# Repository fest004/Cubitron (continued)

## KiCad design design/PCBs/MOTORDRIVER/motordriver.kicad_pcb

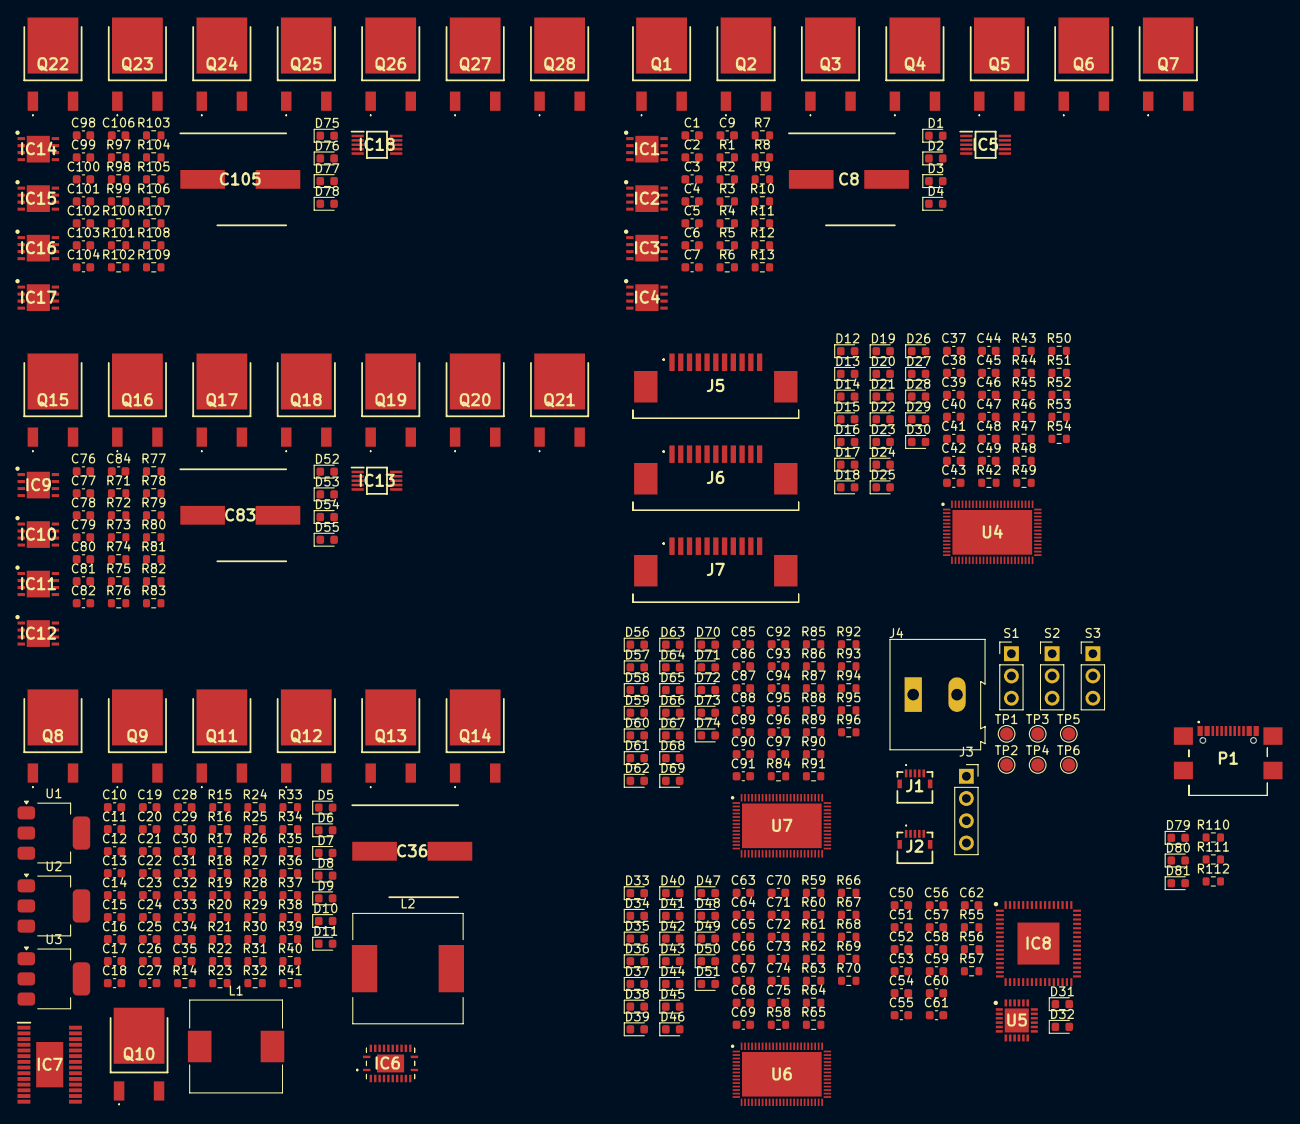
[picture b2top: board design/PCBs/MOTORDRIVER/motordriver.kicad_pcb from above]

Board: 4 copper layers, 371 parts (0 on the bottom side), 222 nets, no tracks yet.

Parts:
C1, C4, C6, C9, C15, C17, C24, C25, C76, C79, C81, C84, C98, C101, C103, C106: 0.1µF; C_0603_1608Metric
C2, C3, C5, C7, C18, C19, C23, C77, C78, C80, C82, C99, C100, C102, C104: 1µF; C_0603_1608Metric
C8, C36, C83, C105: 220µF 35V; CAPAE1050X1050N
C10, C16, C22, C34, C35, C40, C41, C42, C43, C44, C45, C46, C47, C48, C50, C52, C54, C56, C58, C60, C62, C66, C67, C68, C69, C70, C71, C72, C73, C74, C88, C89, C90, C91, C92, C93, C94, C95, C96: 100nF; C_0603_1608Metric
C11, C12: 2.2µF; C_0603_1608Metric
C13, C20, C26: 10uF; C_0603_1608Metric
C14, C27, C28, C51, C53, C55, C57, C59: 10µF; C_0603_1608Metric
C21: 0.047µF; C_0603_1608Metric
C29, C49, C75, C97: 10nF; C_0603_1608Metric
C30: 33nF; C_0603_1608Metric
C31: 470pF; C_0603_1608Metric
C32: 15nF; C_0603_1608Metric
C33: 220pF; C_0603_1608Metric
C37, C38, C39, C63, C64, C65, C85, C86, C87: 100pF; C_0603_1608Metric
C61: 4.7µF; C_0603_1608Metric
D1, D2, D3, D4, D54, D55, D56, D57, D78, D79, D80, D81: 20Vr 5A; D_0603_1608Metric
D5, D6, D8, D11, D12, D13, D14, D15, D16, D17, D18, D19, D20, D21, D22, D23, D24, D25, D30, D31, D34, D35, D36, D37, D38, D39, D40, D41, D42, D43, D44, D45, D46, D47, D52, D53, D58, D59, D60, D61, D62, D63, D64, D65, D66, D67, D68, D69, D70, D71, D76, D77: 470mV 500mA; D_0603_1608Metric
D7, D26, D27, D28, D32, D33, D48, D49, D50, D72, D73, D74: LED; D_0603_1608Metric
D9: PWR; D_0603_1608Metric
D10: 385mV 500mA; D_0603_1608Metric
D29, D51, D75: STATUS; D_0603_1608Metric
IC1, IC2, IC3, IC4, IC9, IC10, IC11, IC12, IC14, IC15, IC16, IC17: LM5109BSDX_NOPB; SON80P400X400X80-9N
IC5, IC13, IC18: INA2181A2IDGSR; SOP50P490X110-10N
IC6: BQ24133RGYR
IC7: LM5176PWPR; SOP65P640X120-29N
IC8: ATSAME53J18A-MF; QFN50P900X900X100-65N-D
J1: IMU1; 59453052110ECHLF
J2: IMU2; 59453052110ECHLF
J3: Conn_01x04_Socket; PinSocket_1x04_P2.54mm_Vertical
J4: Screw_Terminal_01x02; TerminalBlock_Altech_AK300-2_P5.00mm
J5, J6, J7: 1-84952-1; 1849521
L1: 3.3µH; L_10.4x10.4_H4.8
L2: 1µH 420µΩ; L_12x12mm_H8mm
P1: USB_C_Plug_USB2.0; USB4110GFA
Q1, Q2, Q3, Q4, Q5, Q6, Q7, Q8, Q9, Q11, Q12, Q13, Q14, Q15, Q16, Q17, Q18, Q19, Q20, Q21, Q22, Q23, Q24, Q25, Q26, Q27, Q28: 30V 71A; IPD047N03LF2SATMA1
Q10: 40V 70A; IPD70P04P4L08ATMA2
R1, R4, R7, R73, R76, R79, R100, R103, R106: 5Ω; R_0603_1608Metric
R2, R3, R5, R6, R8, R9, R10, R11, R74, R75, R77, R78, R80, R81, R82, R83, R101, R102, R104, R105, R107, R108, R109, R110: 4.7Ω; R_0603_1608Metric
R12, R13, R84, R85, R111, R112: 0.01Ω; R_0603_1608Metric
R14, R30: 10Ω; R_0603_1608Metric
R15: 2Ω; R_0603_1608Metric
R16: 1MΩ; R_0603_1608Metric
R17, R26, R54, R71, R98: 100kΩ; R_0603_1608Metric
R18, R55, R72, R99: 1.5kΩ; R_0603_1608Metric
R19, R22: 4.02kΩ; R_0603_1608Metric
R20: 5.23kΩ; R_0603_1608Metric
R21: 30.1kΩ; R_0603_1608Metric
R23: 20mΩ; R_0603_1608Metric
R24: 232kΩ; R_0603_1608Metric
R25, R27: 32.4kΩ; R_0603_1608Metric
R28, R31, R45, R46, R47, R49, R50, R51, R52, R56, R57, R62, R63, R64, R66, R67, R68, R69, R89, R90, R91, R93, R94, R95, R96: 1kΩ; R_0603_1608Metric
R29: 10mΩ; R_0603_1608Metric
R32: 240kΩ; R_0603_1608Metric
R33: 133kΩ; R_0603_1608Metric
R34: 93.1kΩ; R_0603_1608Metric
R35: 23.2kΩ; R_0603_1608Metric
R36: 280kΩ; R_0603_1608Metric
R37: 2kΩ; R_0603_1608Metric
R38: 20kΩ; R_0603_1608Metric
R39: 9.09kΩ; R_0603_1608Metric
R40, R48, R53, R58, R65, R70, R92, R97: 10kΩ; R_0603_1608Metric
R41: 2mΩ; R_0603_1608Metric
R42, R43, R44, R59, R60, R61, R86, R87, R88: 4.7kΩ; R_0603_1608Metric
S1, S2, S3: PinHeader_1x03_P2.54mm_Vertical
TP1: RX; TestPoint_Pad_D1.5mm
TP2: TX; TestPoint_Pad_D1.5mm
TP3, TP6: GND; TestPoint_Pad_D1.5mm
TP4: SWCLK; TestPoint_Pad_D1.5mm
TP5: SWDIO; TestPoint_Pad_D1.5mm
U1: LD1117S25TR_SOT223; SOT-223-3_TabPin2
U2: LD1117S33TR_SOT223; SOT-223-3_TabPin2
U3: LD1117S50TR_SOT223; SOT-223-3_TabPin2
U4, U6, U7: TMC4671-LA; QFN40P1050X650X90-77N
U5: ATSAMD11D14A-M; QFN50P400X400X90-25N-D

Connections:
+2.5V: C13.1, D16.2 (A), D17.1 (K), D18.2 (A), D19.1 (K), D38.2 (A), D39.1 (K), D40.2 (A), D41.1 (K), D62.2 (A), D63.1 (K), D64.2 (A), D65.1 (K), IC5.5 (REF1), IC5.6 (REF2), IC13.5 (REF1), IC13.6 (REF2), IC18.5 (REF1), IC18.6 (REF2), U1.2 (VO), U4.17 (ADC_I0_NEG), U4.19 (ADC_I1_NEG), U6.17 (ADC_I0_NEG), U6.19 (ADC_I1_NEG), U7.17 (ADC_I0_NEG), U7.19 (ADC_I1_NEG)
+3.3V: C20.1, C40.2, C41.2, C43.2, C44.2, C46.2, C47.2, C50.1, C51.1, C52.1, C53.1, C54.1, C55.1, C56.1, C57.1, C58.1, C59.1, C62.2, C66.2, C67.2, C69.2, C70.2, C72.2, C73.2, C88.2, C89.2, C91.2, C92.2, C94.2, C95.2, IC8.8 (VDDANA), IC8.21 (VDDIOB), IC8.34 (VDDIO_1), IC8.48 (VDDIO_2), IC8.56 (VDDIO_3), J1.2, J2.2, J3.2, R31.2, R53.2, R58.2, R70.2, R97.2, U2.2 (VO), U4.2 (VCCIO1), U4.13 (VCCIO2), U4.44 (GNDIO3), U4.52 (VCCIO4), U4.61 (VCCIO5), U4.72 (VCCIO6), U5.24 (VDD), U6.2 (VCCIO1), U6.13 (VCCIO2), U6.44 (GNDIO3), U6.52 (VCCIO4), U6.61 (VCCIO5), U6.72 (VCCIO6), U7.2 (VCCIO1), U7.13 (VCCIO2), U7.44 (GNDIO3), U7.52 (VCCIO4), U7.61 (VCCIO5), U7.72 (VCCIO6)
+5V: C9.2, C26.1, C84.2, C106.2, D12.1 (K), D14.1 (K), D16.1 (K), D18.1 (K), D20.1 (K), D22.1 (K), D24.1 (K), D30.1 (K), D34.1 (K), D36.1 (K), D38.1 (K), D40.1 (K), D42.1 (K), D44.1 (K), D46.1 (K), D52.1 (K), D58.1 (K), D60.1 (K), D62.1 (K), D64.1 (K), D66.1 (K), D68.1 (K), D70.1 (K), D76.1 (K), IC5.10 (VS), IC13.10 (VS), IC18.10 (VS), R42.1, R43.1, R44.1, R59.1, R60.1, R61.1, R86.1, R87.1, R88.1, S1.2, S2.2, S3.2, U3.2 (VO), U4.23 (V5), U6.23 (V5), U7.23 (V5)
+12V: C2.1, C3.1, C5.1, C7.1, C8.1 (+), C36.1 (+), C77.1, C78.1, C80.1, C82.1, C83.1 (+), C99.1, C100.1, C102.1, C104.1, C105.1 (+), D4.1 (K), D57.1 (K), D81.1 (K), IC1.1 (VDD), IC2.1 (VDD), IC3.1 (VDD), IC4.1 (VDD), IC7.12 (VOSNS), IC7.24 (BIAS), IC9.1 (VDD), IC10.1 (VDD), IC11.1 (VDD), IC12.1 (VDD), IC14.1 (VDD), IC15.1 (VDD), IC16.1 (VDD), IC17.1 (VDD), J5.11, J6.11, J7.11, Q2.2 (D), Q4.2 (D), Q6.2 (D), Q13.2 (D), Q16.2 (D), Q18.2 (D), Q20.2 (D), Q23.2 (D), Q25.2 (D), Q27.2 (D), R1.1, R4.1, R7.1, R11.1, R36.2, R54.1, R71.1, R73.1, R76.1, R79.1, R83.1, R98.1, R100.1, R103.1, R106.1, R110.1
/IO/BATTVIN: C25.2, C27.1, C28.1, D5.2 (A), IC6.15 (SRN), J4.1, Q10.2 (D), R29.1
/IO/OLED_SCL: IC8.17 (PA08), J3.4
/IO/OLED_SDA: IC8.18 (PA09), J3.3
/IO/SWCLK: IC8.58 (PA31), TP4.1
/IO/SWDIO: IC8.57 (PA30), TP5.1
/IO/USBVIN: D6.2 (A), Q8.2 (D), R15.2, R16.2
/driverIC1/ADC_I0_POS: D34.2 (A), D35.1 (K), IC13.1 (OUT1), U6.16 (ADC_I0_POS)
/driverIC1/ADC_I1_POS: D36.2 (A), D37.1 (K), IC13.9 (OUT2), U6.18 (ADC_I1_POS)
/driverIC1/BRAKE: IC11.3 (LI), U6.31 (BRAKE)
/driverIC1/ENI: R65.1, U6.55 (ENI)
/driverIC1/HALL_U: C63.2, D46.2 (A), D47.1 (K), R59.2, R64.1, R64.2, U6.38 (HALL_UX)
/driverIC1/HALL_V: C64.2, D44.2 (A), D45.1 (K), J6.8, R60.2, R63.1, R63.2, U6.37 (HALL_V)
/driverIC1/HALL_W: C65.2, D42.2 (A), D43.1 (K), R61.2, R62.1, R62.2, U6.36 (HALL_WY)
/driverIC2/ADC_I0_POS: D58.2 (A), D59.1 (K), IC18.1 (OUT1), U7.16 (ADC_I0_POS)
/driverIC2/ADC_I1_POS: D60.2 (A), D61.1 (K), IC18.9 (OUT2), U7.18 (ADC_I1_POS)
/driverIC2/BRAKE: IC16.3 (LI), U7.31 (BRAKE)
/driverIC2/ENI: R92.1, U7.55 (ENI)
/driverIC2/HALL_U: C85.2, D70.2 (A), D71.1 (K), R86.2, R91.1, R91.2, U7.38 (HALL_UX)
/driverIC2/HALL_V: C86.2, D68.2 (A), D69.1 (K), J5.8, R87.2, R90.1, R90.2, U7.37 (HALL_V)
/driverIC2/HALL_W: C87.2, D66.2 (A), D67.1 (K), R88.2, R89.1, R89.2, U7.36 (HALL_WY)
/driverIC/ADC_I0_POS: D12.2 (A), D13.1 (K), IC5.1 (OUT1), U4.16 (ADC_I0_POS)
/driverIC/ADC_I1_POS: D14.2 (A), D15.1 (K), IC5.9 (OUT2), U4.18 (ADC_I1_POS)
/driverIC/BRAKE: IC3.3 (LI), U4.31 (BRAKE)
/driverIC/ENI: R48.1, U4.55 (ENI)
/driverIC/HALL_U: C37.2, D24.2 (A), D25.1 (K), R42.2, R47.1, R47.2, U4.38 (HALL_UX)
/driverIC/HALL_V: C38.2, D22.2 (A), D23.1 (K), J7.8, R43.2, R46.1, R46.2, U4.37 (HALL_V)
/driverIC/HALL_W: C39.2, D20.2 (A), D21.1 (K), R44.2, R45.1, R45.2, U4.36 (HALL_WY)
/drivergates1/PHASE_U: J6.1, J6.2
/drivergates1/PHASE_V: J6.3, J6.4
/drivergates1/PHASE_W: J6.5, J6.6, Q20.3 (S), Q21.2 (D)
/drivergates2/PHASE_U: J5.1, J5.2
/drivergates2/PHASE_V: J5.3, J5.4
/drivergates2/PHASE_W: J5.5, J5.6, Q27.3 (S), Q28.2 (D)
/drivergates/PHASE_U: J7.1, J7.2
/drivergates/PHASE_V: J7.3, J7.4
/drivergates/PHASE_W: J7.5, J7.6, Q6.3 (S), Q7.2 (D)
/microcontrollers/ERRLED: IC8.64 (PB03), R56.2
/microcontrollers/PROCLED: IC8.63 (PB02), R57.2
/voltageregulators/HDRV1: IC7.27 (HDRV1), Q11.1 (G)
/voltageregulators/HDRV2: IC7.19 (HDRV2), Q13.1 (G)
/voltageregulators/IC5_VREF: C18.1, IC6.12 (VREF), IC6.14 (CELL), R18.1, R20.2, R24.2, R26.2
/voltageregulators/LDRV1: IC7.25 (LDRV1), Q12.1 (G)
/voltageregulators/LDRV2: IC7.21 (LDRV2), Q14.1 (G)
/voltageregulators/SW1: C34.2, IC7.28 (SW1), L2.1, Q11.3 (S), Q12.2 (D)
/voltageregulators/SW2: C35.2, IC7.18 (SW2), L2.2, Q13.3 (S), Q14.2 (D)
GND: C2.2, C3.2, C5.2, C7.2, C8.2 (-), C9.1, C10.2, C11.2, C12.2, C13.2, C14.2, C15.2, C16.2, C18.2, C19.2, C20.2, C22.2, C23.2, C24.1, C26.2, C27.2, C28.2, C29.2, C30.1, C31.1, C32.1, C33.1, C36.2 (-), C37.1, C38.1, C39.1, C40.1, C41.1, C42.1, C43.1, C44.1, C45.1, C46.1, C47.1, C48.1, C49.1, C50.2, C51.2, C52.2, C53.2, C54.2, C55.2, C56.2, C57.2, C58.2, C59.2, C60.2, C61.2, C62.1, C63.1, C64.1, C65.1, C66.1, C67.1, C68.1, C69.1, C70.1, C71.1, C72.1, C73.1, C74.1, C75.1, C77.2, C78.2, C80.2, C82.2, C83.2 (-), C84.1, C85.1, C86.1, C87.1, C88.1, C89.1, C90.1, C91.1, C92.1, C93.1, C94.1, C95.1, C96.1, C97.1, C99.2, C100.2, C102.2, C104.2, C105.2 (-), C106.1, D9.1 (K), D13.2 (A), D15.2 (A), D17.2 (A), D19.2 (A), D21.2 (A), D23.2 (A), D25.2 (A), D26.1 (K), D27.1 (K), D28.1 (K), D29.1 (K), D31.2 (A), D32.1 (K), D33.1 (K), D35.2 (A), D37.2 (A), D39.2 (A), D41.2 (A), D43.2 (A), D45.2 (A), D47.2 (A), D48.1 (K), D49.1 (K), D50.1 (K), D51.1 (K), D53.2 (A), D59.2 (A), D61.2 (A), D63.2 (A), D65.2 (A), D67.2 (A), D69.2 (A), D71.2 (A), D72.1 (K), D73.1 (K), D74.1 (K), D75.1 (K), D77.2 (A), IC1.4 (VSS), IC2.4 (VSS), IC3.4 (VSS), IC4.4 (VSS), IC5.4 (GND), IC6.22 (PGND_1), IC6.23 (PGND_2), IC6.25 (AGND), IC7.5 (DITH), IC7.10 (AGND), IC7.13 (ISNS(-)), IC7.14 (ISNS(+)), IC7.22 (PGND), IC8.7 (GNDANA), IC8.22 (GND_1), IC8.33 (GND_2), IC8.47 (GND_3), IC8.54 (GND_4), IC9.4 (VSS), IC10.4 (VSS), IC11.4 (VSS), IC12.4 (VSS), IC13.4 (GND), IC14.4 (VSS), IC15.4 (VSS), IC16.4 (VSS), IC17.4 (VSS), IC18.4 (GND), J1.1, J2.1, J3.1, J4.2, J5.7, J6.7, J7.7, Q1.3 (S), Q3.3 (S), Q5.3 (S), Q7.3 (S), Q15.3 (S), Q17.3 (S), Q19.3 (S), Q21.3 (S), Q22.3 (S), Q24.3 (S), Q26.3 (S), Q28.3 (S), R17.1, R21.1, R25.2, R27.1, R33.1, R34.1, R35.1, R38.1, R41.1, R48.2, R55.2, R65.2, R72.2, R92.2, R99.2, S1.1, S2.1, S3.1, TP3.1, TP6.1, U1.1 (GND), U2.1 (GND), U3.1 (GND), U4.3 (GNDIO1), U4.14 (GNDIO2), U4.24 (GNDA), U4.43 (VCCIO3), U4.53 (GNDIO4), U4.54 (TEST), U4.62 (GNDIO5), U4.73 (GNDIO6), U4.77 (GND), U5.25 (GND_2), U6.3 (GNDIO1), U6.14 (GNDIO2), U6.24 (GNDA), U6.43 (VCCIO3), U6.53 (GNDIO4), U6.54 (TEST), U6.62 (GNDIO5), U6.73 (GNDIO6), U6.77 (GND), U7.3 (GNDIO1), U7.14 (GNDIO2), U7.24 (GNDA), U7.43 (VCCIO3), U7.53 (GNDIO4), U7.54 (TEST), U7.62 (GNDIO5), U7.73 (GNDIO6), U7.77 (GND)
unnamed: C11.1, R15.1
unnamed: C30.2, R39.1
unnamed: D1.2 (A), R1.2
unnamed: C1.2, D1.1 (K), IC1.8 (HB)
unnamed: D2.2 (A), R4.2
unnamed: C4.2, D2.1 (K), IC2.8 (HB)
unnamed: D3.2 (A), R7.2
unnamed: C6.2, D3.1 (K), IC4.8 (HB)
unnamed: D4.2 (A), Q1.2 (D), R11.2
unnamed: D5.1 (K), D6.1 (K), R14.2
unnamed: D7.2 (A), R18.2
unnamed: D7.1 (K), IC6.9 (STAT)
unnamed: C14.1, C17.2, C19.1, D8.2 (A), IC6.2 (PVCC_1), IC6.3 (PVCC_2), IC6.5 (ACN), Q10.3 (S), Q11.2 (D), R23.1, R32.2, R37.2
unnamed: D8.1 (K), R30.2
unnamed: D9.2 (A), R31.1
unnamed: D10.2 (A), D11.2 (A), IC7.23 (VCC), R40.1
unnamed: C35.1, D10.1 (K), IC7.20 (BOOT2)
unnamed: C34.1, D11.1 (K), IC7.26 (BOOT1)
unnamed: D26.2 (A), R49.1
unnamed: D27.2 (A), R50.1
unnamed: D28.2 (A), R51.1
unnamed: D29.2 (A), R52.1
unnamed: C49.2, D30.2 (A), D31.1 (K), R54.2, R55.1, U4.20 (ADC_VM)
unnamed: D32.2 (A), R56.1
unnamed: D33.2 (A), R57.1
unnamed: D48.2 (A), R66.1
unnamed: D49.2 (A), R67.1
unnamed: D50.2 (A), R68.1
unnamed: D51.2 (A), R69.1
unnamed: C75.2, D52.2 (A), D53.1 (K), R71.2, R72.1, U6.20 (ADC_VM)
unnamed: D54.2 (A), R73.2
unnamed: C76.2, D54.1 (K), IC9.8 (HB)
unnamed: D55.2 (A), R76.2
unnamed: C79.2, D55.1 (K), IC10.8 (HB)
unnamed: D56.2 (A), R79.2
unnamed: C81.2, D56.1 (K), IC12.8 (HB)
unnamed: D57.2 (A), Q15.2 (D), R83.2
unnamed: D72.2 (A), R93.1
unnamed: D73.2 (A), R94.1
unnamed: D74.2 (A), R95.1
unnamed: D75.2 (A), R96.1
unnamed: C97.2, D76.2 (A), D77.1 (K), R98.2, R99.1, U7.20 (ADC_VM)
unnamed: D78.2 (A), R100.2
unnamed: C98.2, D78.1 (K), IC14.8 (HB)
unnamed: D79.2 (A), R103.2
unnamed: C101.2, D79.1 (K), IC15.8 (HB)
unnamed: D80.2 (A), R106.2
unnamed: C103.2, D80.1 (K), IC17.8 (HB)
unnamed: D81.2 (A), Q22.2 (D), R110.2
unnamed: IC1.7 (HO), R2.1
unnamed: C1.1, IC1.6 (HS)
unnamed: IC1.5 (LO), R3.2
unnamed: IC2.7 (HO), R5.1
unnamed: C4.1, IC2.6 (HS)
unnamed: IC2.5 (LO), R6.2
unnamed: IC3.5 (LO), R9.2
unnamed: IC4.7 (HO), R8.1
unnamed: C6.1, IC4.6 (HS)
unnamed: IC4.5 (LO), R10.2
unnamed: IC5.3 (IN+1), R12.2
unnamed: IC5.7 (IN+2), R13.2
unnamed: IC6.8 (ACDRV), R19.1
unnamed: C17.1, IC6.6 (ACP), Q8.3 (S), Q9.2 (D), Q9.3 (S), R22.2, R23.2
unnamed: IC6.17 (ACSET), R26.1, R27.2
unnamed: C12.1, IC6.4 (AVCC), R14.1
unnamed: C21.1, IC6.21 (BTST)
unnamed: IC6.7 (CMSRC), R22.1
unnamed: IC6.13 (ISET), R24.1, R25.1
unnamed: IC6.18 (OVPSET), R16.1, R17.2
unnamed: C23.1, IC6.20 (REGN)
unnamed: C24.2, C25.1, IC6.16 (SRP), L1.2, R29.2
unnamed: C21.2, IC6.1 (SW_1), IC6.24 (SW_2), L1.1
unnamed: IC6.10 (TS), R20.1, R21.2
unnamed: C15.1, IC6.11 (TTC)
unnamed: IC6.19 (~BATDRV), R28.2
unnamed: C31.2, IC7.9 (COMP), R39.2
unnamed: IC7.15 (CSG), R41.2
unnamed: IC7.1 (EN/UVLO), R32.1, R33.2
unnamed: IC7.11 (FB), R36.1, R38.2
unnamed: IC7.4 (MODE), R34.2
unnamed: IC7.17 (PGOOD), R40.2
unnamed: IC7.6 (RT), R35.2
unnamed: C33.2, IC7.7 (SLOPE)
unnamed: C32.2, IC7.8 (SS)
unnamed: C29.1, IC7.2 (VIN), R30.1
unnamed: IC7.3 (VISNS), R37.1
unnamed: C60.1, C61.1, IC8.53 (VDDCORE)
unnamed: IC9.7 (HO), R74.1
unnamed: C76.1, IC9.6 (HS)
unnamed: IC9.5 (LO), R75.2
unnamed: IC10.7 (HO), R77.1
unnamed: C79.1, IC10.6 (HS)
unnamed: IC10.5 (LO), R78.2
unnamed: IC11.5 (LO), R81.2
unnamed: IC12.7 (HO), R80.1
unnamed: C81.1, IC12.6 (HS)
unnamed: IC12.5 (LO), R82.2
unnamed: IC13.3 (IN+1), R84.2
unnamed: IC13.7 (IN+2), R85.2
unnamed: IC14.7 (HO), R101.1
unnamed: C98.1, IC14.6 (HS)
unnamed: IC14.5 (LO), R102.2
unnamed: IC15.7 (HO), R104.1
unnamed: C101.1, IC15.6 (HS)
unnamed: IC15.5 (LO), R105.2
unnamed: IC16.5 (LO), R108.2
unnamed: IC17.7 (HO), R107.1
unnamed: C103.1, IC17.6 (HS)
unnamed: IC17.5 (LO), R109.2
unnamed: IC18.3 (IN+1), R111.2
unnamed: IC18.7 (IN+2), R112.2
unnamed: Q1.1 (G), R9.1
unnamed: Q2.1 (G), R8.2
unnamed: Q2.3 (S), Q3.2 (D), R12.1
unnamed: Q3.1 (G), R10.1
unnamed: Q4.1 (G), R5.2
unnamed: Q4.3 (S), Q5.2 (D), R13.1
unnamed: Q5.1 (G), R6.1
unnamed: Q6.1 (G), R2.2
unnamed: Q7.1 (G), R3.1
unnamed: Q8.1 (G), Q9.1 (G), R19.2
unnamed: Q10.1 (G), R28.1
unnamed: Q12.3 (S), Q14.3 (S)
unnamed: Q15.1 (G), R81.1
unnamed: Q16.1 (G), R80.2
unnamed: Q16.3 (S), Q17.2 (D), R84.1
unnamed: Q17.1 (G), R82.1
unnamed: Q18.1 (G), R77.2
unnamed: Q18.3 (S), Q19.2 (D), R85.1
unnamed: Q19.1 (G), R78.1
unnamed: Q20.1 (G), R74.2
unnamed: Q21.1 (G), R75.1
unnamed: Q22.1 (G), R108.1
unnamed: Q23.1 (G), R107.2
unnamed: Q23.3 (S), Q24.2 (D), R111.1
unnamed: Q24.1 (G), R109.1
unnamed: Q25.1 (G), R104.2
unnamed: Q25.3 (S), Q26.2 (D), R112.1
unnamed: Q26.1 (G), R105.1
unnamed: Q27.1 (G), R101.2
unnamed: Q28.1 (G), R102.1
unnamed: C10.1, U1.3 (VI)
unnamed: C16.1, U2.3 (VI)
unnamed: C22.1, U3.3 (VI)
unnamed: R49.2, U4.1 (GPIO5_/_AENC_UX_MCD_/_DBGSPI_MOSI)
unnamed: R50.2, U4.4 (GPIO6_/_AENC_VN_MCD_/_DBGSPI_MISO)
unnamed: R51.2, U4.5 (GPIO7_/_AENC_WY_MCD_/_DBGSPI_TRG)
unnamed: R53.1, U4.50 (NRST)
unnamed: R52.2, U4.12 (STATUS)
unnamed: C48.2, U4.15 (VCCCORE1)
unnamed: C45.2, U4.45 (VCCCORE2)
unnamed: C42.2, U4.63 (VCCCORE3)
unnamed: R58.1, U5.18 (PA28/~RESET)
unnamed: R66.2, U6.1 (GPIO5_/_AENC_UX_MCD_/_DBGSPI_MOSI)
unnamed: R67.2, U6.4 (GPIO6_/_AENC_VN_MCD_/_DBGSPI_MISO)
unnamed: R68.2, U6.5 (GPIO7_/_AENC_WY_MCD_/_DBGSPI_TRG)
unnamed: R70.1, U6.50 (NRST)
unnamed: R69.2, U6.12 (STATUS)
unnamed: C74.2, U6.15 (VCCCORE1)
unnamed: C71.2, U6.45 (VCCCORE2)
unnamed: C68.2, U6.63 (VCCCORE3)
unnamed: R93.2, U7.1 (GPIO5_/_AENC_UX_MCD_/_DBGSPI_MOSI)
unnamed: R94.2, U7.4 (GPIO6_/_AENC_VN_MCD_/_DBGSPI_MISO)
unnamed: R95.2, U7.5 (GPIO7_/_AENC_WY_MCD_/_DBGSPI_TRG)
unnamed: R97.1, U7.50 (NRST)
unnamed: R96.2, U7.12 (STATUS)
unnamed: C96.2, U7.15 (VCCCORE1)
unnamed: C93.2, U7.45 (VCCCORE2)
unnamed: C90.2, U7.63 (VCCCORE3)
SPI_MISO: IC8.28 (PB15), U4.9 (SPI_MISO), U6.9 (SPI_MISO), U7.9 (SPI_MISO)
SPI_MOSI: IC8.27 (PB14), U4.8 (SPI_MOSI), U6.8 (SPI_MOSI), U7.8 (SPI_MOSI)
SPI_SCK: IC8.26 (PB13), U4.7 (SPI_SCK), U6.7 (SPI_SCK), U7.7 (SPI_SCK)

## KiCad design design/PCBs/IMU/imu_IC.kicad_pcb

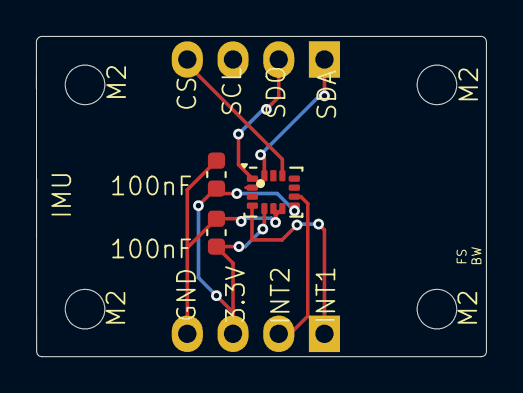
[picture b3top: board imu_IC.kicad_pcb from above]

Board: 2 copper layers, 25.0 x 17.8 mm, 9 parts (0 on the bottom side), 7 nets.

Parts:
C1, C2: C; C_0603_1608Metric
H1, H2, H3, H4: MountingHole_Pad; MountingHole_2.2mm_M2
J1, J2: Conn_01x04; FanPinHeader_1x04_P2.54mm_Vertical
U1: ISM330DHCX; LGA-14_3x2.5mm_P0.5mm_LayoutBorder3x4y

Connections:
+3.3V: C1.1, C2.1, J2.3, U1.5 (VDDIO), U1.8 (VDD)
CS: J1.4, U1.12 (CS)
GND: C1.2, C2.2, J2.4, U1.6 (GND), U1.7 (GND)
INT1: J2.1, U1.4 (INT1)
INT2: J2.2, U1.9 (INT2)
SDA: J1.1, U1.14 (SDA)
SDO/SAO: J1.2, U1.1 (SDO/SA0)

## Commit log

2024-09-14 added CAD file with one face started
2024-09-14 added docs
2024-09-14 Deploy website - based on 9b167ce7eeb336958f770d9337f480f18a3490d9
2024-09-15 Flywheel design started
2024-09-15 updated docs
2024-09-15 Deploy website - based on 9d93d528c595d8dd281faff51109269124de136a
2024-09-15 Further progress on flywheel
2024-09-15 IMU Chip first draft, just needs to be looked over by someone
2024-09-16 Rounded corners, removed pin symbol noise
2024-09-16 updated docs and added motordriver pcb
2024-09-16 updated readme and restructured
2024-09-16 restructuring
2024-09-16 File restructure, IMU PCB updated
2024-09-16 Deploy website - based on 5697a8d69320431a6c5de3d1d40be5786416be5d
2024-09-16 update docs
2024-09-16 fixed imu pcb offset
2024-09-16 Removed kicad folder, replaced with PCB folder
2024-09-16 Deploy website - based on 5281ae26820e0452b0b5a8cde7f52178727e83f1
2024-09-17 Flywheel 2.1
2024-09-18 update motordriver
2024-09-18 made another version of a flywheel
2024-09-18 Deploy website - based on 03bc33c42d6b1779f4bc1d522a76eabaee914897
2024-09-21 Testing subsection for docs, little bit of detail on first prototype
2024-09-23 updated fonts
2024-09-23 Deploy website - based on a2814eaac738b5dcc1dc3aa078df309d6883770a
2024-09-23 Deploy website - based on 4dad8df97ff1ee3006db84052415156897631eb3
2024-09-24 updated motordriver and gitignore to not track backups
2024-09-24 updated gitignore
2024-09-24 added src folder
2024-09-27 Motor holder, V2 cube face
2024-09-27 Flywheel 2.0
2024-09-28 Adjusted tolerances based on physical measurements
2024-09-28 Flywheel diameter adjusted to fit into cubeface
2024-09-29 updated cad model
2024-10-05 Deploy website - based on 44ed4bee3f5642ee3e8dc6af2953ee0f0f365f0c
2024-10-05 updated docs and added tooling for arduino testing (makefile with build and upload stages)
2024-10-09 added some general files, mostly work on math stuff that will be nice to have
2024-10-11 reconciled src files
2024-10-11 worked on motor pcb
2024-10-11 moved controller pcb to a single unified pcb, added more work on motordriver
2024-10-15 added color to CAD model
2024-10-18 iterative pcb update
2024-10-18 progress
2024-10-18 added reference schematic for inspiration
2024-10-19 cleaned up documentation
2024-10-19 fixed deploy script
2024-10-19 fixed deploy script again..
2024-10-19 MCU added, x-ed some motordriver pins
2024-10-19 removed docs
2024-10-19 updated PCB
2024-10-19 synced with gitignore
2024-10-19 cortex added, fixed some symbols in motordriver file
2024-10-19 fixed merge
2024-10-23 added programmer
2024-10-24 USB-C schematics to programmer, programmer to cortex-4 added
2024-10-24 First draft of programmer added. GPIO pins are axed atm but can be included if we want some extra functionality, like indicator LEDs or similar.
    Routing from USB-C to programmer to main cortex are added. Also
    added some datasheets and sources.
2024-10-25 Docs testing for myself
2024-10-25 12 to 3.3 LDO added, temporary 5 to 12 reg added
2024-10-25 added battery charger
2024-10-28 5V ref IC changed to correct one
2024-10-31 Clearer file names for datasheets indicating what kind of component they are. Started on connecting the battery charger Added mosfet ICs for driver gates
2024-11-01 Motor headers added, mosfet datasheets
2024-11-01 Mosfet symbol added
2024-11-01 added gates
2024-11-01 added gate driver
2024-11-02 fixed schematic layout and added shunt resistor and zener diodes for motor stage
2024-11-03 added lables and worked on the motor stage, changed the mosfet driver
2024-11-03 changed mosfets to work with 12v gate
2024-11-07 drove up some hierarchial connections in root sheet
2024-11-09 added oled header and connected to microcontroller. progress on vreg
2024-11-10 added power ic
2024-11-10 This battery charger is killing me.
    Completed 8/24 pins
    Following are completed:
    VREF
    TTC
    TS
    STAT
2024-11-11 more
2024-11-11 added correct analog voltage lables
2024-11-11 cleaned up lurking gitingore files
2024-11-15 romoved analog ground
2024-11-16 cleaned up libraries
2024-11-16 Added micro-servo headers Added header for FFC cable IMU PCB
    We need to set IMU PCB input to correspond to
    the one we have made here.
2024-11-16 merge
2024-11-16 changed voltage regulator
2024-11-16 drivergates IC coupled up
2024-11-17 worked on power and merged programmer and microcontroller sheets
2024-11-17 added back LED
2024-11-18 finished 12v voltage, The components for alost all ICs need values. Cleaned up a bit
2024-11-18 moved some files, and deleted junk
2024-11-18 wrote some docs
2024-12-10 added capacitor values in drivergates
2024-12-10 added capacitor and resistor values in drivergates
2024-12-10 progress on docs
2024-12-11 Removed unneccessary TMC4761 pins
    Finally went through every pin on the TMC and tried to eliminate
    unneeded pins. Reduced sheet complexity quite nicely. Pretty much
    all rationales for removing pins were added to the design document,
    although not formatted that nicely yet.
2024-12-12 Switched TMC hall sensor input to digital from motors
2024-12-12 TMC and MCU connections
    Further progress on PCB. Main remainders are:
    Voltage regulator page (couple todos)
    Fix sheet duplication for output sheets
    Decide on UART or SPI debug for TMC
    Formalize stuff, fill out bottom right on sheets
2024-12-15 documentation, values, double-checking stuff
2024-12-15 added power reference document
2024-12-15 component values for lm51
2024-12-16 removed compile commands file
2024-12-16 cleaned up, added values and footprints
2024-12-16 changed vreferences with LDOs
2024-12-16 uart for tmc-mcu comms
2024-12-16 cleaned up
2024-12-16 fixed references
2024-12-18 new footprint and symbol system. added more footprints
2024-12-19 looked over
2024-12-19 cleaned pcb components
2024-12-19 worked on schematic
2024-12-20 Started on software
    State machine structure is laid out.
    TMC4671 drivers are taken from official software.
    IMU drivers are taken from portalspace/drivers, but are
    not fully configured for our purposes yet.
    Compact Quaternion library has also been added.
2024-12-20 worked on schemtaic
2024-12-21 worked on schemtac
2024-12-21 made clearer foldernames and cleaned up
2024-12-22 removed backup files and found components for special resistors and diodes
2024-12-22 added diodes
2024-12-23 fixed root folder schematics
2024-12-23 Double checked all SERCOM pins
    Finally looked at how SERCOMs work in this chip, what the PADs
    mean and so on. This allowed me to double check all communication
    pins and make sure all communication between modules are on correct
    peripherals.
2024-12-23 MCU connections double checked/fixed
    Made sure all individual communication lines happens
    on their own SERCOM instance. Made sure all PWM signals are on
    PWM compatible pins, same for interrupts.
2024-12-23 small tweaks
2024-12-23 tmc gpio pins fixed, spi db fixed, all mcu digital pins fixed, decoupled resetn
2024-12-23 added inductors
2024-12-23 double checked SERCOM again, as well as PWM and interrupt pin capabilities
2024-12-24 started on mcu drivers
2024-12-24 removed firmware dir
2024-12-27 minor tweaks on schematic and started on the pcb layout, made good work
2024-12-28 worked on PCB
2025-01-04 compiled baby
2025-01-05 renamed some files in makefile script
2025-01-05 added design rules from pcbway, we need to redo some work to fit the design rules
2025-01-06 software
2025-01-06 added external oscillator files
2025-01-06 peripheral clocks
2025-01-07 pre rework of pwr planes to save if something goes wrong
2025-01-07 sw and hw lmao
    worked on drivers mainly. added oscillator to schematic.
2025-01-07 layout rework, better ground plane
2025-01-07 folder rename
2025-01-07 Test code, interrupts, TCC
    Added some test code for toggling an LED on the
    V2 nav board. Unfortunately dont have AA batteries
    ...
    interrupt pins are configured, but im very unsure of the
    implementation, will look more into
    also added pwm pin configuration for motor control. not implemented
2025-01-08 had to redo some work :<
2025-01-10 worked on pcb and added led to programmer and jumpers to swd line
2025-01-18 - worked on pcb
2025-01-18 Cleaned up folders added more software stuff
2025-01-18 dap software compiles, need to be configured correctly tho
2025-01-19 worked on cmsis dap implementation aswell as cleaned up startup files for both microcontrolers
2025-01-19 worked on cmsis dap
2025-01-19 cmsis dap is done, jsut needs to be tested
2025-01-20 12v is connected, refactored some docs
2025-01-21 pcb done
2025-01-26 added new brake chopper logic, the previous was sketchy, still we might need to find better brake resistors than the one I added
2025-02-21 motor holder progress, need 2 add fastening point
2025-02-21 shaft hub started. unsure of screw holes mainly
2025-02-27 saved here
2025-02-27 shaft hub v1 exported
2025-02-27 added cornermount
2025-02-27 assembly of motor holder with faces
2025-02-27 tested asembly
2025-03-01 shaft hub v2, flywheel updated
2025-03-01 added bom
2025-03-01 flywheel and shaft fitted
2025-03-01 added assembly
2025-03-02 cleanup
2025-03-05 Motor holder fastening
    Added correct length from center of motor holder
    to edge of cube. Added holes in correct place. As
    well
    The thickness of the cube will probably have to be adjusted.
    I do not have the energy to find out how to flip them in
    the assembly. The "cube" is pointing the wrong way.
2025-03-06 motor holder hole and support added
2025-03-06 assembly
2025-03-08 removed pullup resistor on swdio as it is too small
2025-03-14 started work on pcbv2 work in progress
2025-04-14 updated sch
2025-10-01 added simulation script
